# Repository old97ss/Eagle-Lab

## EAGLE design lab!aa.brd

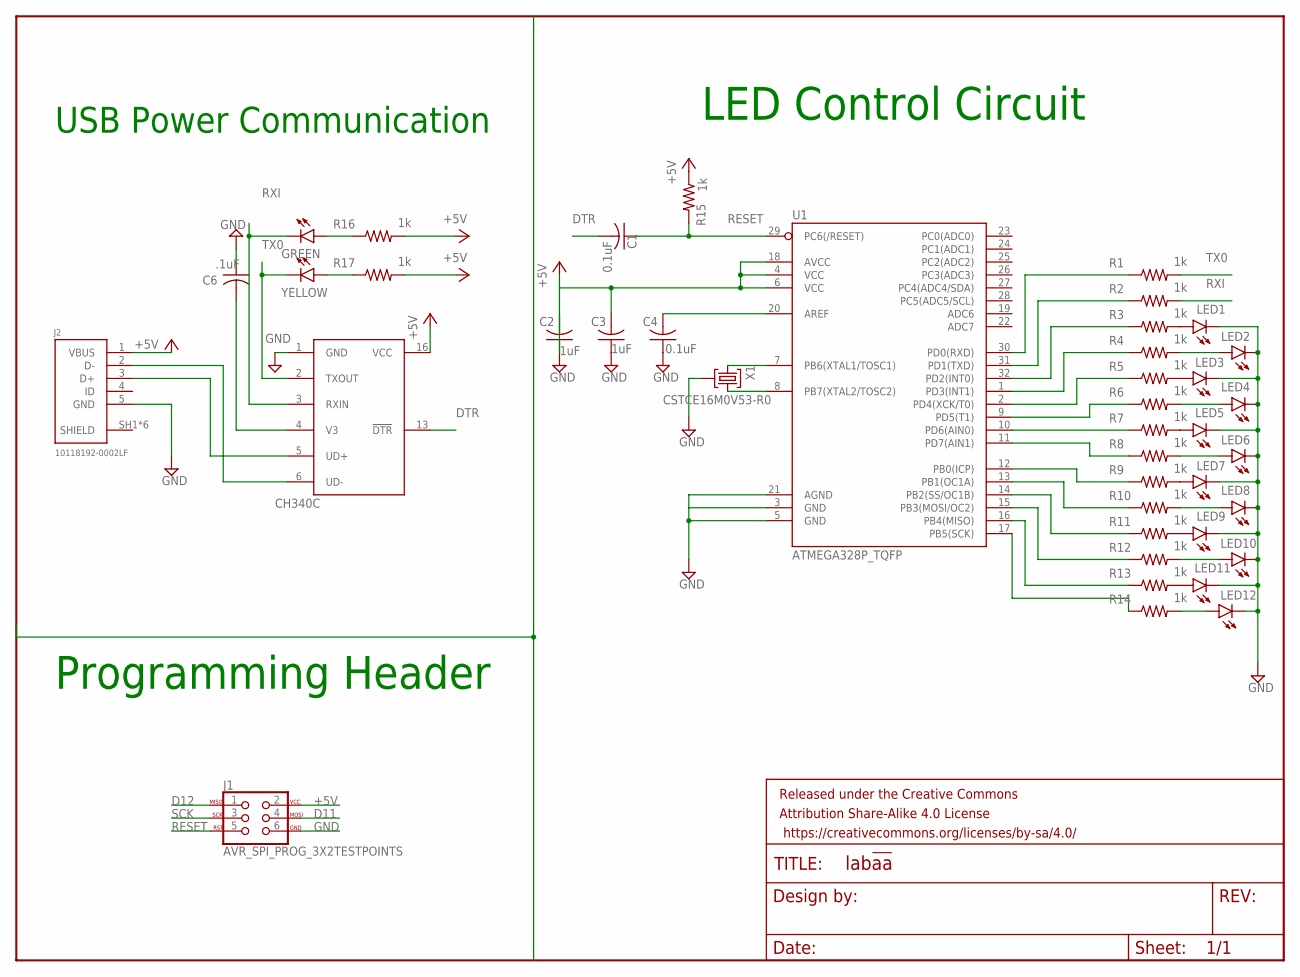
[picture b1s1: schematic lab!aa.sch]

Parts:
C1, C4: 0.1uF; C0805
C2, C3: 1uF; C0805
C6: .1uF; C0805
FRAME1: FRAME-LETTERNO_PACKAGE; DUMMY
GREEN: LEDCHIP-LED0805; CHIP-LED0805
J1: AVR_SPI_PROG_3X2TESTPOINTS; 2X3_TEST_POINTS
J2: 10118192-0002LF
LED1, LED2, LED3, LED4, LED5, LED6, LED7, LED8, LED9, LED10, LED11, LED12: LEDCHIP-LED0805; CHIP-LED0805
R1, R2, R3, R4, R5, R6, R7, R8, R9, R10, R11, R12, R13, R14, R15, R16, R17: 1k; M0805
U1: ATMEGA328P_TQFP; TQFP32-08
U$1: CH340C; SOP16
X1: CSTCE16M0V53-R0
YELLOW: LEDCHIP-LED0805; CHIP-LED0805

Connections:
+5V: J1.2, J2.1 (VBUS), R15.1, R16.2, R17.2, U$1.16 (VCC)
D11: J1.4
D12: J1.1
DTR: C1.2, U$1.13 (!DTR)
GND: C2.1, C2.2, C3.1, C3.2, C4.1, C6.1, J1.6, J2.5 (GND), LED1.C, LED2.C, LED3.C, LED4.C, LED5.C, LED6.C, LED7.C, LED8.C, LED9.C, LED10.C, LED11.C, LED12.C, U1.3 (GND), U1.4 (VCC), U1.5 (GND), U1.6 (VCC), U1.7 (PB6(XTAL1/TOSC1)), U1.18 (AVCC), U1.21 (AGND), U$1.1 (GND), X1.1 (INPUT), X1.2 (GND)
unnamed: R1.1, U1.30 (PD0(RXD))
unnamed: R2.1, U1.31 (PD1(TXD))
unnamed: R3.1, U1.32 (PD2(INT0))
unnamed: R4.1, U1.1 (PD3(INT1))
unnamed: R5.1, U1.2 (PD4(XCK/T0))
unnamed: R6.1, U1.9 (PD5(T1))
unnamed: R7.1, U1.10 (PD6(AIN0))
unnamed: R8.1, U1.11 (PD7(AIN1))
unnamed: R9.1, U1.12 (PB0(ICP))
unnamed: R10.1, U1.13 (PB1(OC1A))
unnamed: R11.1, U1.14 (PB2(SS/OC1B))
unnamed: R12.1, U1.15 (PB3(MOSI/OC2))
unnamed: R13.1, U1.16 (PB4(MISO))
unnamed: R14.1, U1.17 (PB5(SCK))
unnamed: LED1.A, R3.2
unnamed: LED2.A, R4.2
unnamed: LED11.A, R13.2
unnamed: LED9.A, R11.2
unnamed: LED7.A, R9.2
unnamed: LED4.A, R6.2
unnamed: LED5.A, R7.2
unnamed: LED3.A, R5.2
unnamed: LED12.A, R14.2
unnamed: LED10.A, R12.2
unnamed: LED8.A, R10.2
unnamed: LED6.A, R8.2
unnamed: C4.2, U1.20 (AREF)
unnamed: U1.8 (PB7(XTAL2/TOSC2)), X1.3 (OUTPUT)
unnamed: J2.2 (D-), U$1.6 (UD-)
unnamed: J2.3 (D+), U$1.5 (UD+)
unnamed: GREEN.A, R16.1
unnamed: R17.1, YELLOW.A
unnamed: C6.2, U$1.4 (V3)
RESET: C1.1, J1.5, R15.2, U1.29 (PC6(/RESET))
RXI: GREEN.C, R2.2, U$1.3 (RXIN)
SCK: J1.3
SHIELD: J2.SH1 (SHIELD), J2.SH2 (SHIELD), J2.SH3 (SHIELD), J2.SH4 (SHIELD), J2.SH5 (SHIELD), J2.SH6 (SHIELD)
TX0: R1.2, U$1.2 (TXOUT), YELLOW.C

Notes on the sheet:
LED Control Circuit
USB Power Communication
Programming Header

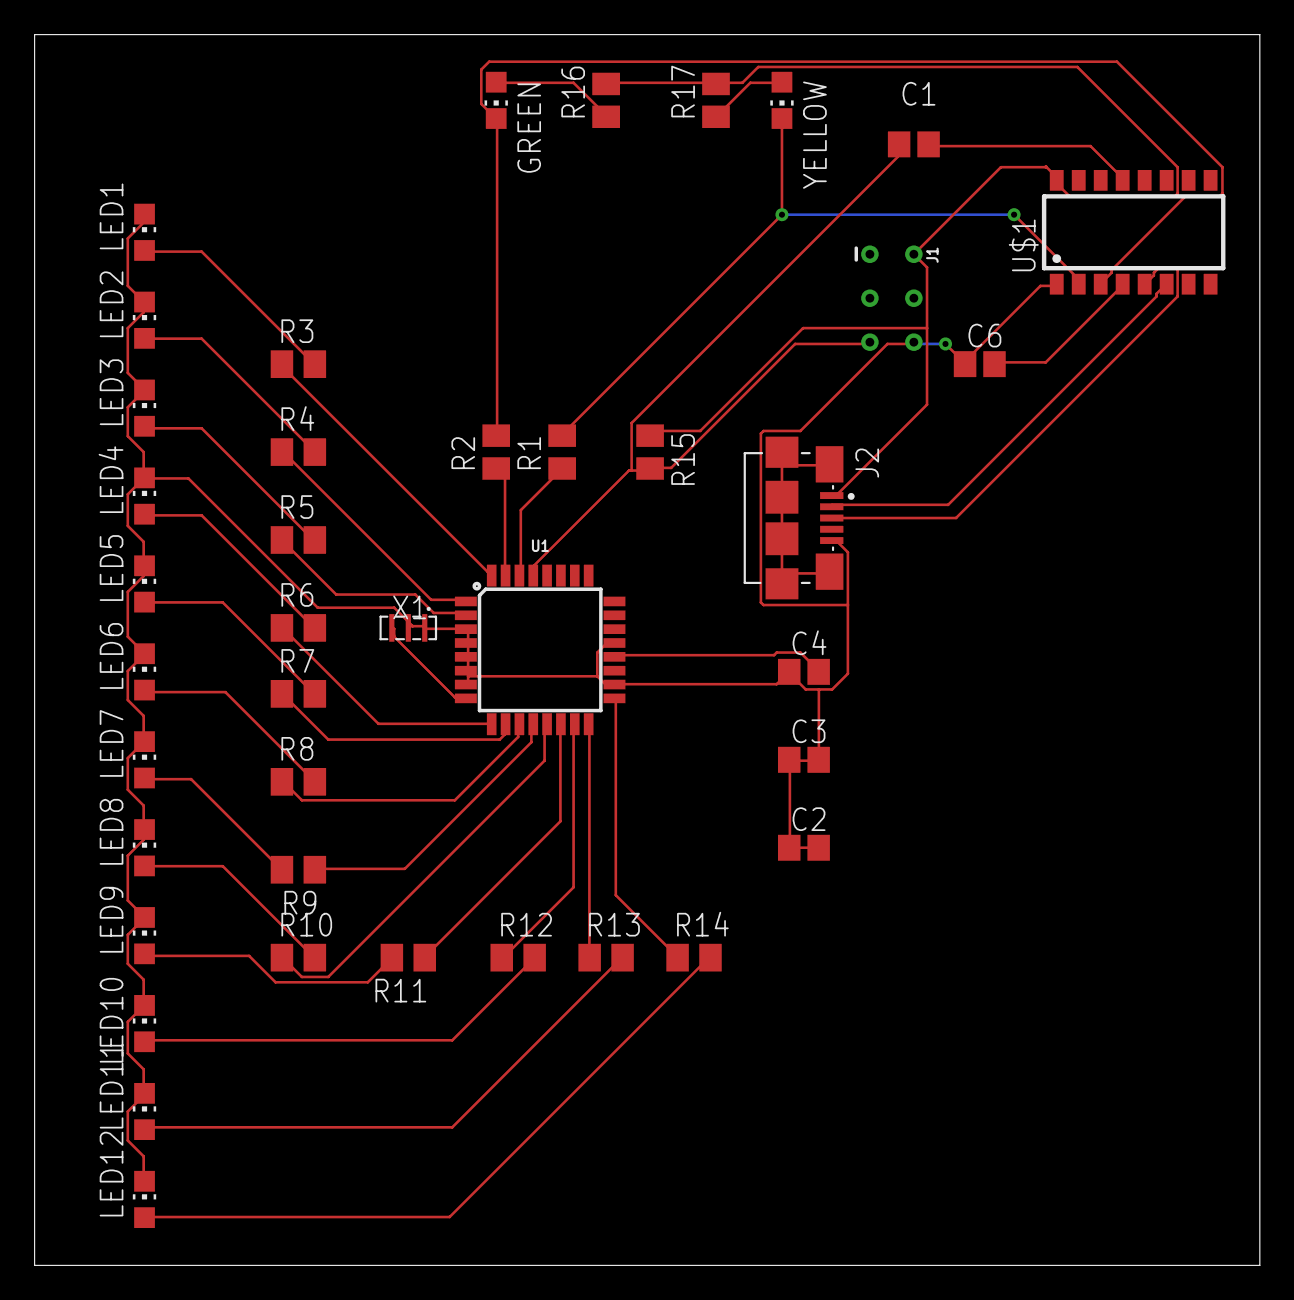
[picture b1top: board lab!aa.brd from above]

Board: 2 copper layers, 70.8 x 71.1 mm, 42 parts (0 on the bottom side), 40 nets.

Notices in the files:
parts and their libraries:
SparkFun-Aesthetics: Licensing: Creative Commons ShareAlike 4.0 International - https://creativecommons.org/licenses/by-sa/4.0
SparkFun-Aesthetics: Released under the Creative Commons Attribution Share-Alike 4.0 License
SparkFun-Aesthetics: https://creativecommons.org/licenses/by-sa/4.0
